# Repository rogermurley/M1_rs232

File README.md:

# M1_rs232
RS-232 interface board for the TRS-80 Model I Expansion Interface, version 2.1

### If you would like to purchase turnkey assembled and tested units, or bare PCBs, please visit my site at https://byteshiftmusic.com/trs-80-model-i-rs-232-interface-re-creation/

I also have available a PCB for adapting the 40-pin edge card (J1) on the Expansion Interface to an IDC26 header, so that a standard PC parallel port DB25 pigtail can be used. Please see the link above for those, as well.

I created this design partly out of necessity, as original Radio Shack serial interfaces are scarce, and partly as a project to learn KiCad.

This design replicates the operation of the original board, ensuring compatibility with existing Model I software. Hardware-wise, there are a few differences:
  1. SMT components are used wherever possible, to minimize cost
  2. Sense switch (DIP switch configuration) functionality is removed, so that the interface must be configured via software
  3. The TERM/COMM switch has been removed. The unit is configured in TERM (DTE) mode, and an external null-modem adapter must be used if operation as a DCE device is required.
  4. IC selection eliminated the need for +12/-12/-5 supply rails. +5V is the only supply needed.

Version 2.1 fixes a nasty error which caused the line driver (U9) to be in permanent shutdown mode, fixes some minor mechanical interference between the PCB and the expansion interface's chassis, and adds some quality of life enhancements, such as:
 1. A jumper for RS-232 TX/RX loopback was added for ease of testing
 2. A breakout header for TTL-level TX and RX was added, for ease in interfacing to an ESP8266 running [WiFiModem firmware](https://github.com/dhansel/WifiModem)
 3. A breakout header for +5VDC and GND was added for powering the previously mentioned ESP8266
 4. A jumper for disabling the RS-232 transceiver was added, for use when using an internal TTL-level device

BOM notes:
  1. J1 is PCB fingers on the underside of the board, which press-fit against the Expansion Interface add-on connector.
  2. J2, J3, J4, and J5 are standard 2.54mm pitch single row headers, 11 pins in total
  3. Y1 must be an AT-cut series type crystal with an ESR of <= 50 ohms in order to function properly with the 8116 baud rate generator.
  4. U1 and U2 must be purchased used or as old stock. Ebay is a good source.
  5. U2's COM8116 can be substituted with a Western Digital WD1943. Please ensure that the IC that you purchase is the variant (typically with a -00 suffix) which uses a 5.0688 MHz crystal and produces a 16x baud clock. If you have the -05 variant which uses a 4.9152 MHz crystal, this may work by substituting the proper crystal for Y1, but this has not been tested. The -06 variant, which generates a 32x baud clock, will NOT work with this UART.

This project is released under the [CERN Open Hardware Licence Version 2 - Strongly Reciprocal](https://gitlab.com/ohwr/project/cernohl/-/blob/master/licence_texts/cern_ohl_w_v2.txt?ref_type=heads). Copyright 2025 Roger Murley.

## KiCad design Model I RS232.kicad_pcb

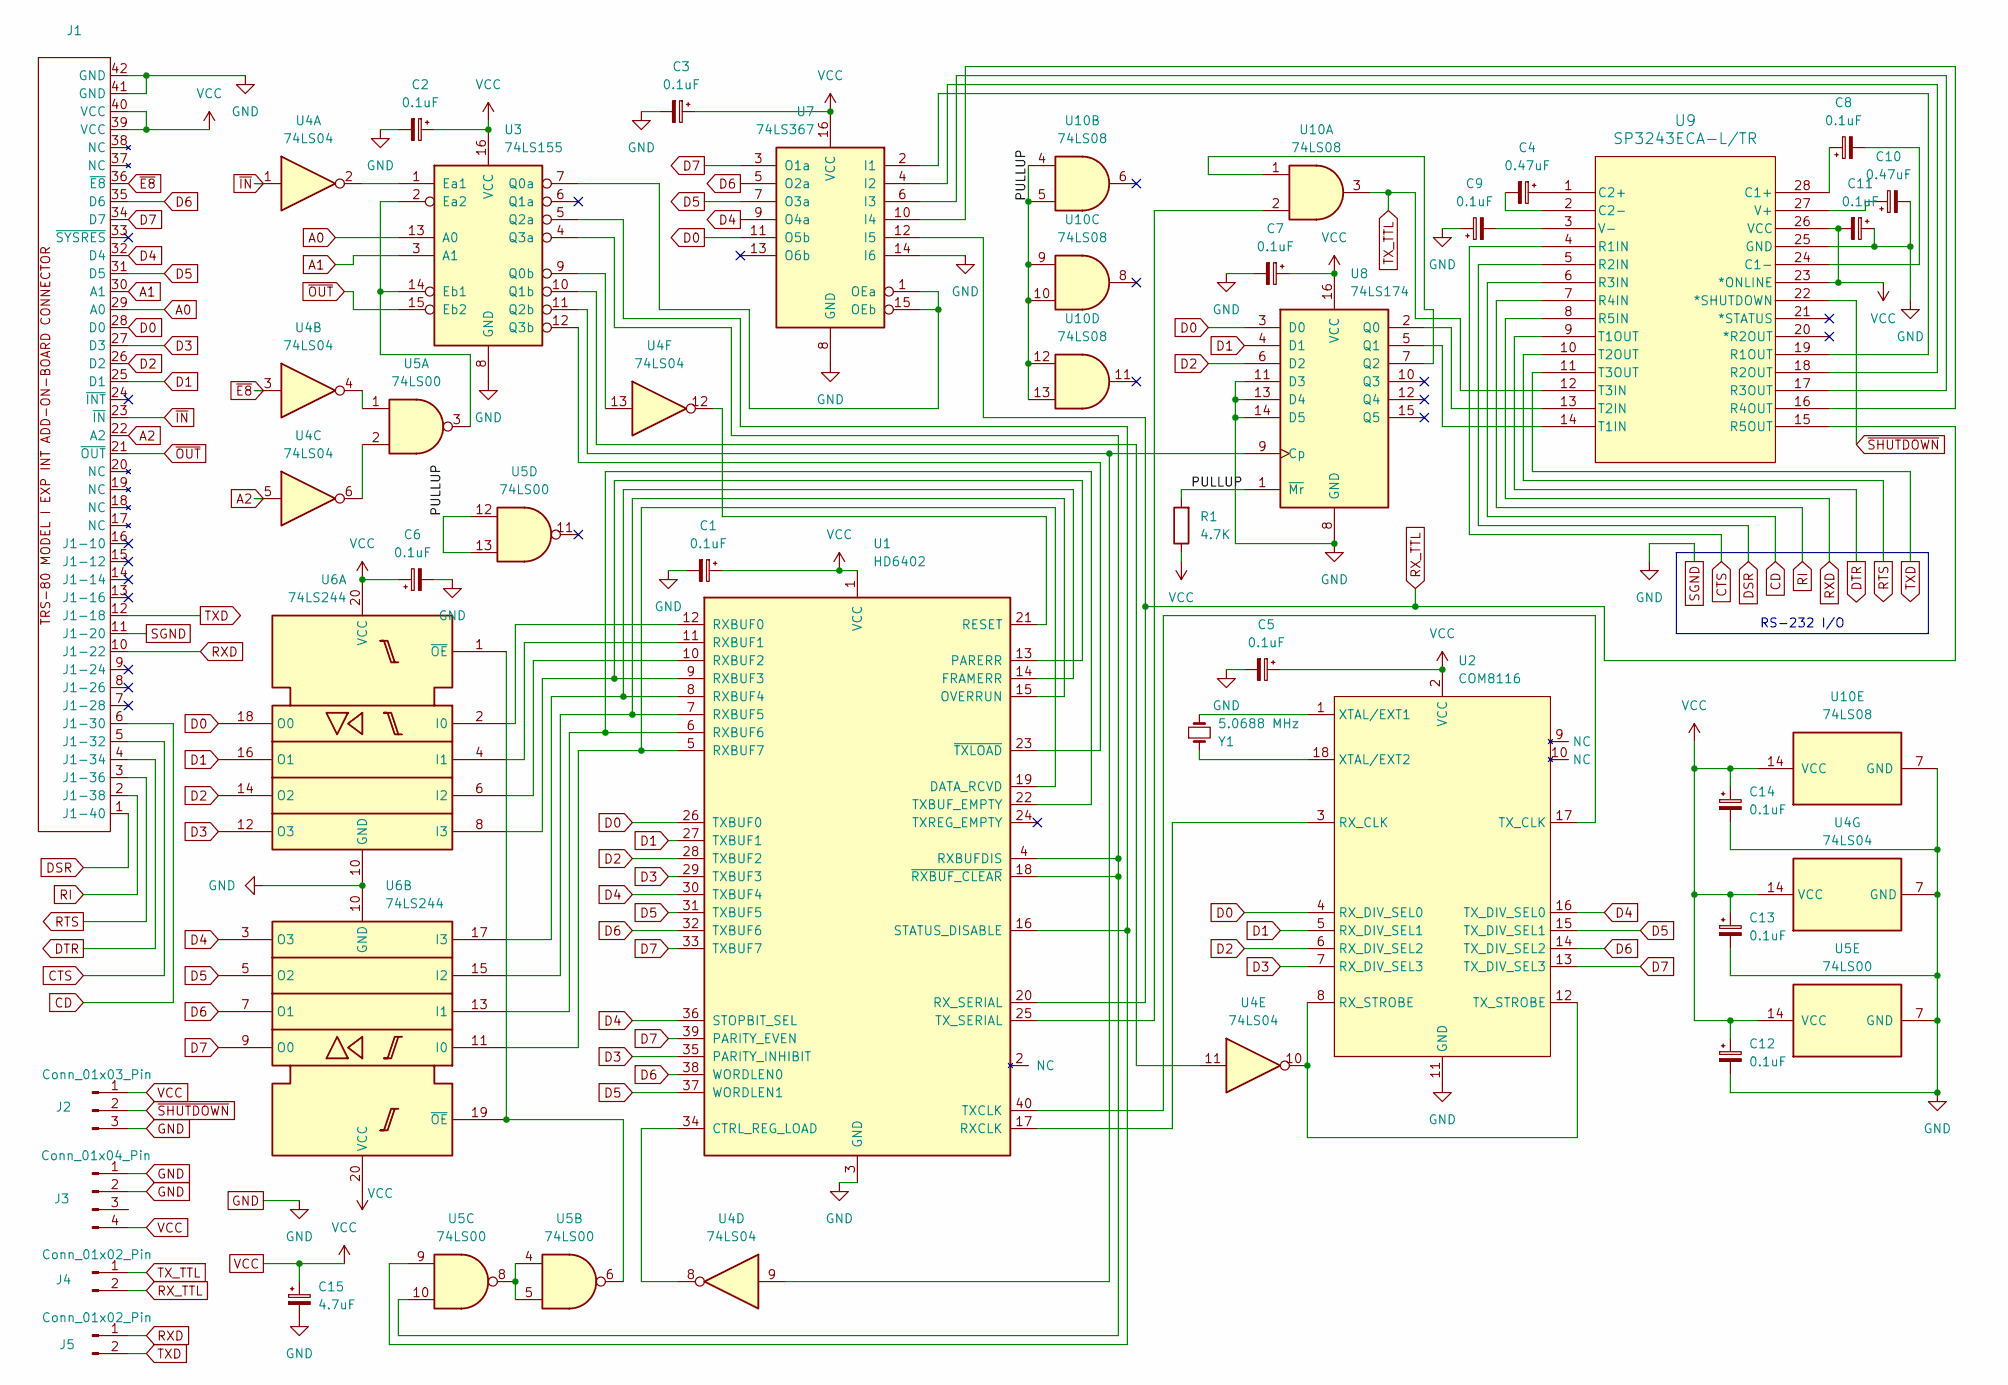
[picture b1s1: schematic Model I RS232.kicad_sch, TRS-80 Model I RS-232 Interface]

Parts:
C1, C2, C3, C5, C6, C7, C8, C9, C11, C12, C13, C14: 0.1uF; C_0805_2012Metric_Pad1.18x1.45mm_HandSolder
C4, C10: 0.47uF; C_0805_2012Metric_Pad1.18x1.45mm_HandSolder
C15: 4.7uF; C_0805_2012Metric_Pad1.18x1.45mm_HandSolder
J1: TRS-80 M1 EI_ADDON_42P_CONN
J2: Conn_01x03_Pin; PinHeader_1x03_P2.54mm_Vertical
J3: Conn_01x04_Pin; PinHeader_1x04_P2.54mm_Vertical
J4, J5: Conn_01x02_Pin; PinHeader_1x02_P2.54mm_Vertical
R1: 4.7K; R_0805_2012Metric_Pad1.20x1.40mm_HandSolder
U1: HD6402; DIP-40_W15.24mm_Socket_LongPads
U2: COM8116; DIP-18_W7.62mm_Socket_LongPads
U3: 74LS155; SOIC-16_3.9x9.9mm_P1.27mm
U4: 74LS04; SOIC-14_3.9x8.7mm_P1.27mm
U5: 74LS00; SOIC-14_3.9x8.7mm_P1.27mm
U6: 74LS244; SOIC-20W_7.5x12.8mm_P1.27mm
U7: 74LS367; SOIC-16_3.9x9.9mm_P1.27mm
U8: 74LS174; SOIC-16_3.9x9.9mm_P1.27mm
U9: SP3243ECA-L/TR; SSOP-28_5.3x10.2mm_P0.65mm
U10: 74LS08; SOIC-14_3.9x8.7mm_P1.27mm
Y1: 5.0688 MHz; Crystal_HC49-U_Horizontal

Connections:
/PULLUP: R1.2, U5.12, U5.13, U8.1 (~Mr), U10.4, U10.5, U10.9, U10.10, U10.12, U10.13
A0: J1.29 (A0), U3.13 (A0)
A1: J1.30 (A1), U3.3 (A1)
A2: J1.22 (A2), U4.5
CD: J1.6 (J1-30), U9.6 (R3IN)
CTS: J1.5 (J1-32), U9.4 (R1IN)
D0: J1.28 (D0), U1.26 (TXBUF0), U2.4 (RX_DIV_SEL0), U6.18 (O0), U7.11 (O5b), U8.3 (D0)
D1: J1.25 (D1), U1.27 (TXBUF1), U2.5 (RX_DIV_SEL1), U6.16 (O1), U8.4 (D1)
D2: J1.26 (D2), U1.28 (TXBUF2), U2.6 (RX_DIV_SEL2), U6.14 (O2), U8.6 (D2)
D3: J1.27 (D3), U1.29 (TXBUF3), U1.35 (PARITY_INHIBIT), U2.7 (RX_DIV_SEL3), U6.12 (O3)
D4: J1.32 (D4), U1.30 (TXBUF4), U1.36 (STOPBIT_SEL), U2.16 (TX_DIV_SEL0), U6.3 (O3), U7.9 (O4a)
D5: J1.31 (D5), U1.31 (TXBUF5), U1.37 (WORDLEN1), U2.15 (TX_DIV_SEL1), U6.5 (O2), U7.7 (O3a)
D6: J1.35 (D6), U1.32 (TXBUF6), U1.38 (WORDLEN0), U2.14 (TX_DIV_SEL2), U6.7 (O1), U7.5 (O2a)
D7: J1.34 (D7), U1.33 (TXBUF7), U1.39 (PARITY_EVEN), U2.13 (TX_DIV_SEL3), U6.9 (O0), U7.3 (O1a)
DSR: J1.1 (J1-40), U9.5 (R2IN)
DTR: J1.4 (J1-34), U9.9 (T1OUT)
GND: C1.2, C2.2, C3.2, C5.2, C6.2, C7.2, C9.1, C10.2, C11.1, C12.2, C13.2, C14.2, C15.2, J1.11 (J1-20), J1.41 (GND), J1.42 (GND), J2.3, J3.1, J3.2, U1.3 (GND), U2.11 (GND), U3.8 (GND), U4.7 (GND), U5.7 (GND), U6.10 (GND), U7.8 (GND), U7.14 (I6), U8.8 (GND), U8.11 (D3), U8.13 (D4), U8.14 (D5), U9.25 (GND), U10.7 (GND)
unnamed: U1.34 (CTRL_REG_LOAD), U4.8
unnamed: U1.5 (RXBUF7), U1.19 (DATA_RCVD), U6.11 (I0)
unnamed: U1.8 (RXBUF4), U1.14 (FRAMERR), U6.17 (I3)
unnamed: U1.7 (RXBUF5), U1.15 (OVERRUN), U6.15 (I2)
unnamed: U1.9 (RXBUF3), U1.13 (PARERR), U6.8 (I3)
unnamed: U1.21 (RESET), U4.12
unnamed: U1.12 (RXBUF0), U6.2 (I0)
unnamed: U1.11 (RXBUF1), U6.4 (I1)
unnamed: U1.10 (RXBUF2), U6.6 (I2)
unnamed: U1.6 (RXBUF6), U1.22 (TXBUF_EMPTY), U6.13 (I1)
unnamed: U1.4 (RXBUFDIS), U1.18 (~RXBUF_CLEAR), U3.4 (Q3a), U5.10
unnamed: U1.17 (RXCLK), U2.3 (RX_CLK)
unnamed: U1.16 (STATUS_DISABLE), U3.5 (Q2a), U5.9
unnamed: U1.40 (TXCLK), U2.17 (TX_CLK)
unnamed: U1.25 (TX_SERIAL), U10.2
unnamed: U1.23 (~TXLOAD), U3.12 (Q3b)
unnamed: U2.8 (RX_STROBE), U2.12 (TX_STROBE), U4.10
unnamed: U2.1 (XTAL/EXT1), Y1.2
unnamed: U2.18 (XTAL/EXT2), Y1.1
unnamed: U3.1 (Ea1), U4.2
unnamed: U3.2 (Ea2), U3.14 (Eb1), U5.3
unnamed: U3.7 (Q0a), U7.1 (OEa), U7.15 (OEb)
unnamed: U3.9 (Q0b), U4.13
unnamed: U3.10 (Q1b), U4.11
unnamed: U3.11 (Q2b), U4.9, U8.9 (Cp)
unnamed: U4.4, U5.1
unnamed: U4.6, U5.2
unnamed: U5.4, U5.5, U5.8
unnamed: U5.6, U6.1 (~OE), U6.19 (~OE)
unnamed: U7.2 (I1), U9.19 (R1OUT)
unnamed: U7.4 (I2), U9.18 (R2OUT)
unnamed: U7.6 (I3), U9.17 (R3OUT)
unnamed: U7.10 (I4), U9.16 (R4OUT)
unnamed: U8.2 (Q0), U9.13 (T2IN)
unnamed: U8.5 (Q1), U9.14 (T1IN)
unnamed: U8.7 (Q2), U10.1
unnamed: C8.1, U9.28 (C1+)
unnamed: C8.2, U9.24 (C1-)
unnamed: C4.1, U9.1 (C2+)
unnamed: C4.2, U9.2 (C2-)
unnamed: C10.1, U9.27 (V+)
unnamed: C9.2, U9.3 (V-)
RI: J1.2 (J1-38), U9.7 (R4IN)
RTS: J1.3 (J1-36), U9.10 (T2OUT)
RXD: J1.10 (J1-22), J5.1, U9.8 (R5IN)
RX_TTL: J4.2, U1.20 (RX_SERIAL), U7.12 (I5), U9.15 (R5OUT)
TXD: J1.12 (J1-18), J5.2, U9.11 (T3OUT)
TX_TTL: J4.1, U9.12 (T3IN), U10.3
VCC: C1.1, C2.1, C3.1, C5.1, C6.1, C7.1, C11.2, C12.1, C13.1, C14.1, C15.1, J1.39 (VCC), J1.40 (VCC), J2.1, J3.4, R1.1, U1.1 (VCC), U2.2 (VCC), U3.16 (VCC), U4.14 (VCC), U5.14 (VCC), U6.20 (VCC), U7.16 (VCC), U8.16 (VCC), U9.23 (*ONLINE), U9.26 (VCC), U10.14 (VCC)
~E8: J1.36 (~E8), U4.3
~IN: J1.23 (~IN), U4.1
~OUT: J1.21 (~OUT), U3.15 (Eb2)
~SHUTDOWN: J2.2, U9.22 (*SHUTDOWN)

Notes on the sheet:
RS-232 I/O

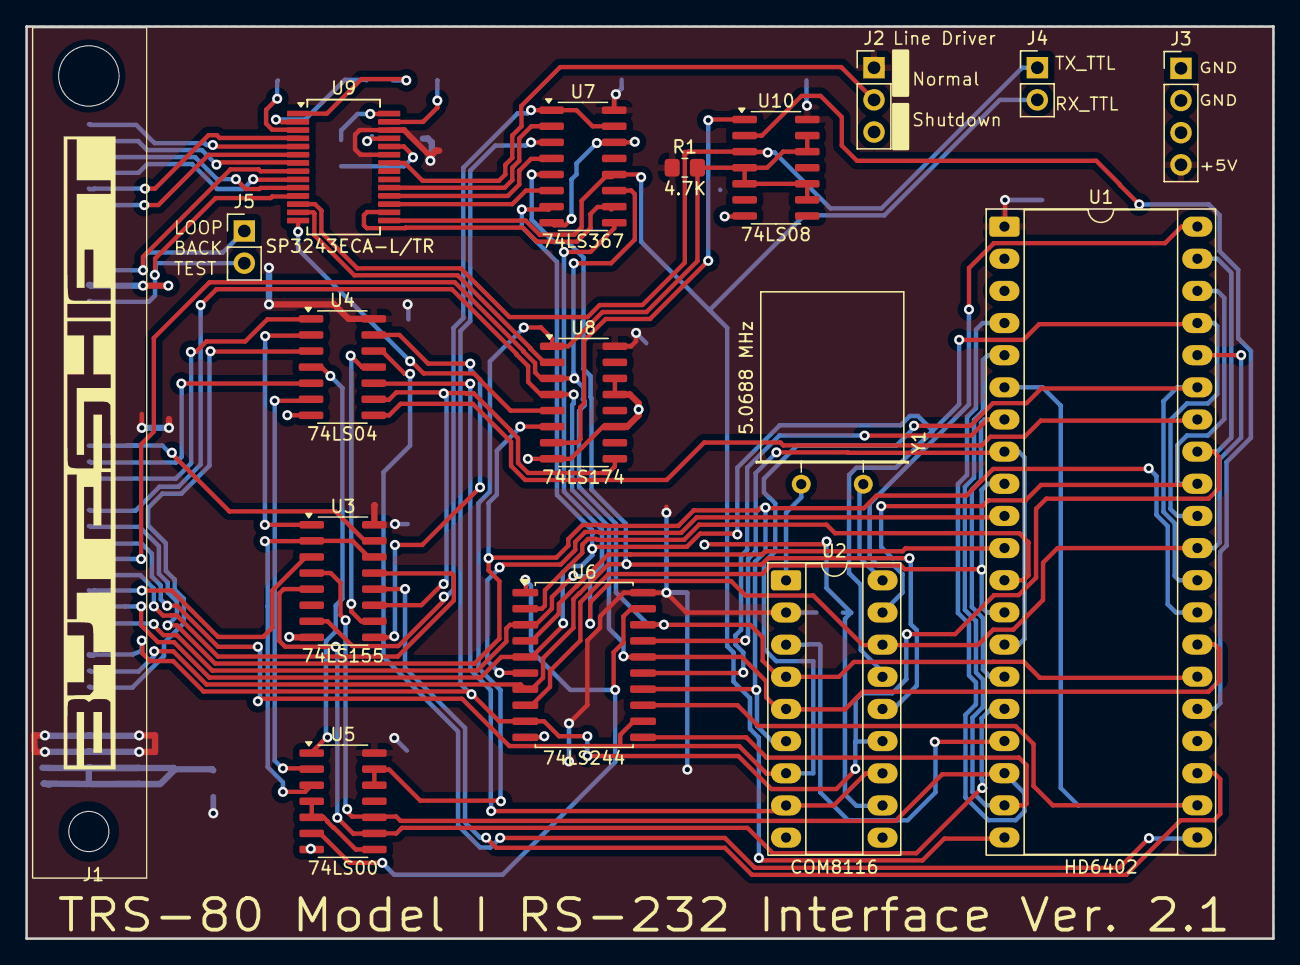
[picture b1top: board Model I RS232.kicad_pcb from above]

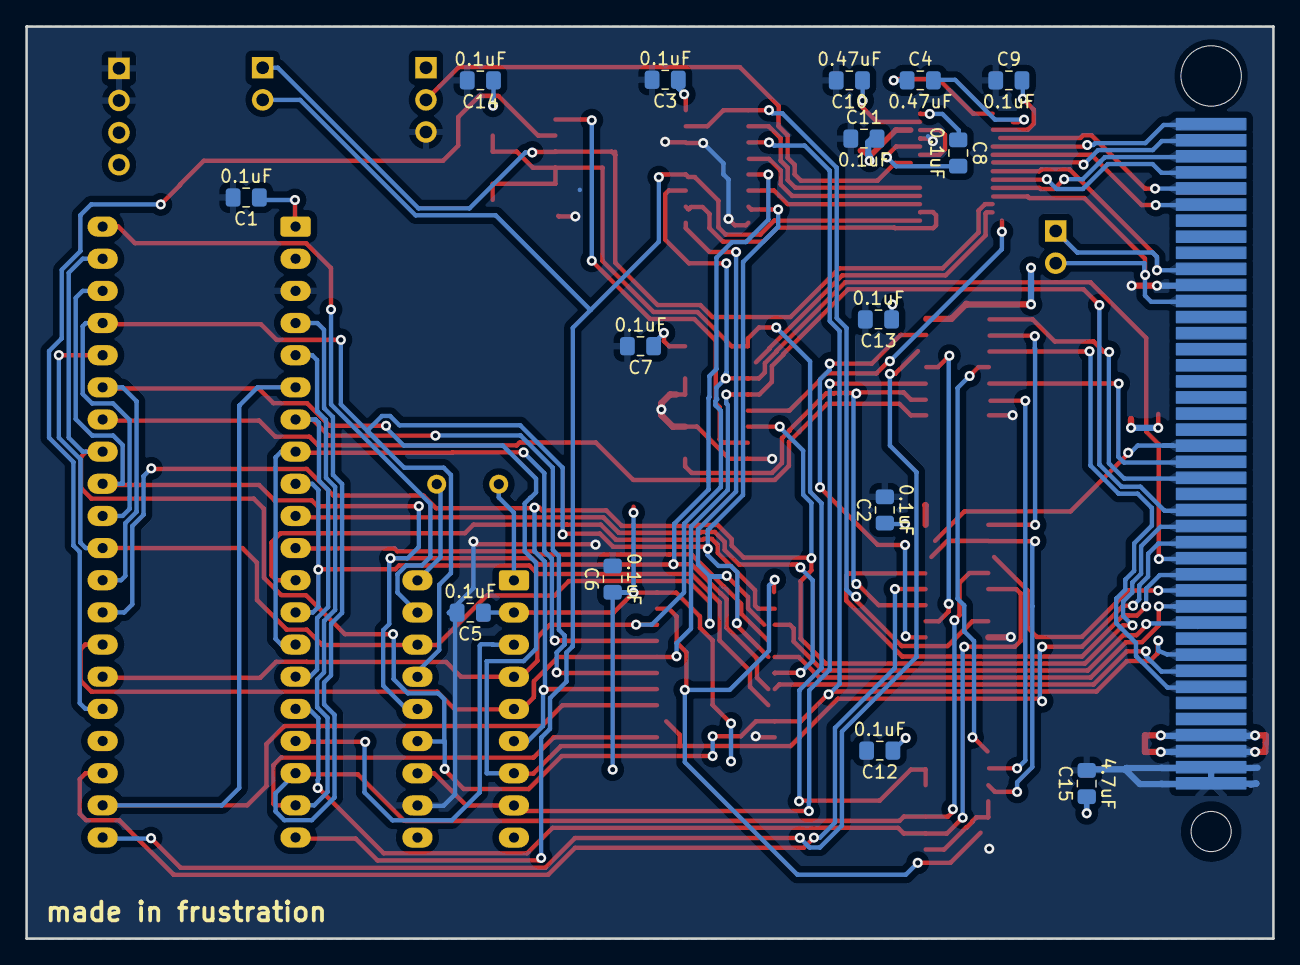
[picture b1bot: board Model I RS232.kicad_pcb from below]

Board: 2 copper layers, 98.5 x 72.1 mm, 32 parts (15 on the bottom side), 70 nets.

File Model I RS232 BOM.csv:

"Reference","Qty","Value","DNP","Exclude from BOM","Exclude from Board","Footprint","Datasheet"
"C1,C2,C3,C5,C6,C7,C8,C9,C12,C13,C14","11","0.1uF","","","","Capacitor_SMD:C_0805_2012Metric_Pad1.18x1.45mm_HandSolder","~"
"C4,C10,C11","3","0.47uF","","","","Capacitor_SMD:C_0805_2012Metric_Pad1.18x1.45mm_HandSolder","~"
"C15","1","4.7uF","","","","Capacitor_THT:C_Radial_D6.3mm_H11.0mm_P2.50mm","~"
"J1","1","~","","","","Byteshift_Library:TRS-80 M1 EI_ADDON_42P_CONN",""
"R1","1","4.7K","","","","Resistor_SMD:R_0805_2012Metric_Pad1.20x1.40mm_HandSolder","~"
"U1","1","HD6402","","","","Package_DIP:DIP-40_W15.24mm_Socket_LongPads",""
"U2","1","COM8116","","","","Package_DIP:DIP-18_W7.62mm_Socket_LongPads",""
"U3","1","74LS155","","","","Package_DIP:DIP-16_W7.62mm_Socket_LongPads","http://www.ti.com/lit/gpn/sn74LS155"
"U4","1","74LS04","","","","Package_SO:SOIC-14_3.9x8.7mm_P1.27mm","http://www.ti.com/lit/gpn/sn74LS04"
"U5","1","74LS00","","","","Package_SO:SOIC-14_3.9x8.7mm_P1.27mm","http://www.ti.com/lit/gpn/sn74ls00"
"U6","1","74LS244","","","","Package_SO:SOIC-20W_7.5x12.8mm_P1.27mm","http://www.ti.com/lit/ds/symlink/sn74ls244.pdf"
"U7","1","74LS367","","","","Package_SO:SOIC-16_3.9x9.9mm_P1.27mm","http://www.ti.com/lit/gpn/sn74LS367"
"U8","1","74LS174","","","","Package_SO:SOIC-16_3.9x9.9mm_P1.27mm","http://www.ti.com/lit/gpn/sn74LS174"
"U9","1","SP3243ECA-L/TR","","","","Package_SO:TSSOP-28_4.4x9.7mm_P0.65mm","SP3243ECA-L/TR"
"U10","1","74LS08","","","","Package_SO:SOIC-14_3.9x8.7mm_P1.27mm","http://www.ti.com/lit/gpn/sn74LS08"
"Y1","1","5.0688 MHz","","","","Crystal:Crystal_HC49-U_Horizontal","~"

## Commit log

2025-03-15 Update README.md
    Initial edit
2025-03-15 Update README.md
    Changed TERM/DTE wording
2025-03-15 Update README.md
    Added BOM notes
2025-03-15 Update README.md
    added 'untested' disclaimer
2025-03-17 Add files via upload
    trimmed PCB size a bit to clear support post
2025-03-17 Add files via upload
    Gerbers recreated after PCB changes
2025-04-05 Delete Model I RS232 Schematic.pdf
    Changing filenames to match KiCAD output
2025-04-05 Delete Model I RS232 BOM.csv
    Changing filenames to match KiCAD output
2025-04-05 Delete Model I RS232 legacy BOM.csv
    Changing filenames to match KiCAD output
2025-04-05 Add files via upload
    Update schematic and PCB to version 1.1 -- 05 April 2025
    1. change PCB footprint to eliminate mechanical interference with mounting post
    2. modify footprint of J1 pads to fit more closely
    3. fix schematic error causing U9 to be in permanent shutdown mode
    4. Clean up some very ugly routing
    5. Change version information on silkscreen
2025-04-05 Update README.md
    Description of version 1.1 changes, and upcoming version 2.0 implementation
2025-04-05 Update README.md
    Added lower-side PCB render
2025-04-06 Add files via upload
    Updated local footprint for J1
2025-04-26 Update README.md
    Add note about incorrect U9 package
2025-05-07 Update README.md
    added info on line 20 specifying series type of crystal for Y1
2025-06-10 Update README.md
    added info on U2 substitution, and noted that bare PCBs are available for sale
2025-06-15 Create license
    CERN Open Hardware Licence Version 2 - Strongly Reciprocal
2025-06-15 Update README.md
    license & copyright
2025-06-15 Update README.md
    added additional notes on substitution of U2
